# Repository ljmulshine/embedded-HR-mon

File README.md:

# embedded-HR-mon
Personal project that improves upon a previous breadboard based HR monitor project of mine.

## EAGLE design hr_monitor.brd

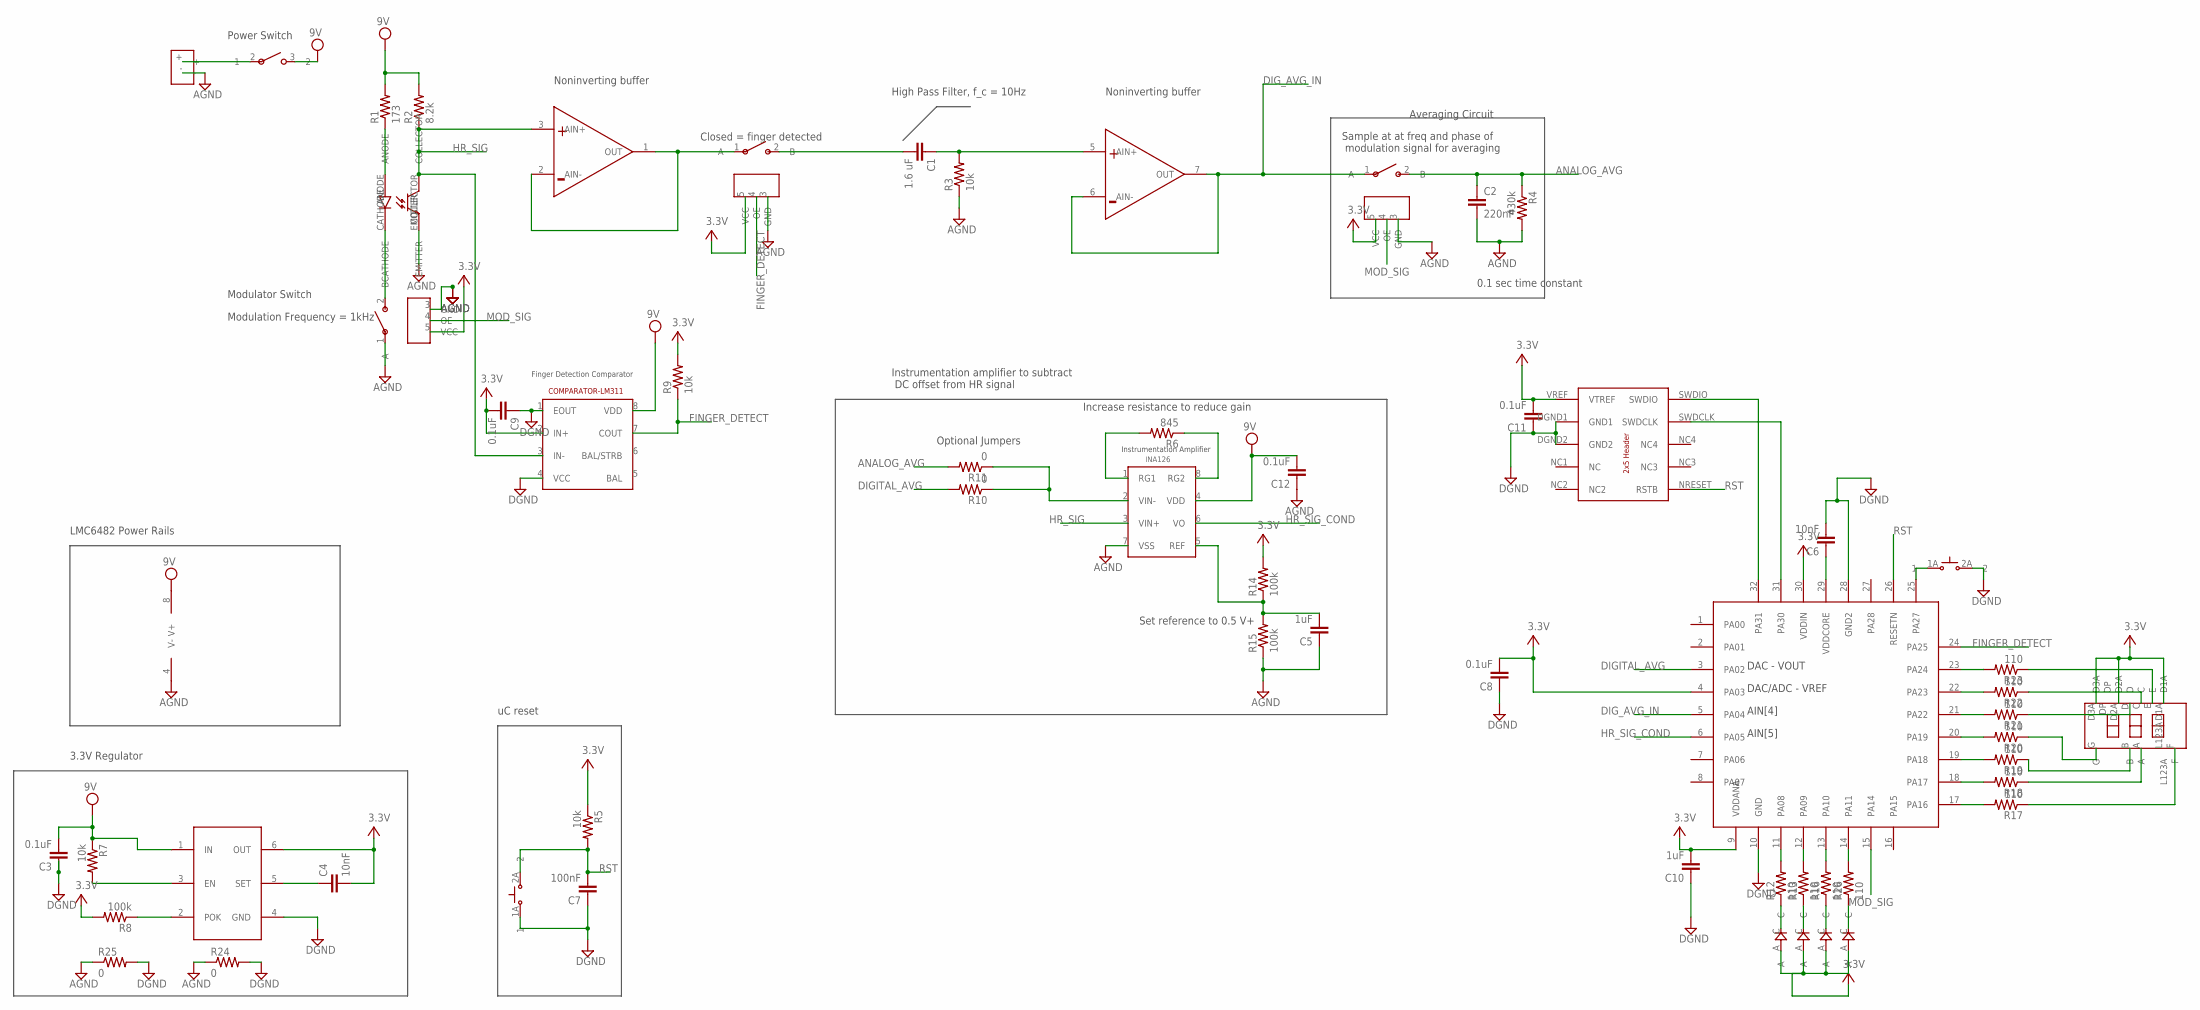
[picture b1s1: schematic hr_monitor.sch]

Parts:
C1: 1.6 uF; C0805
C2: 220nF; C0805
C3, C8, C9, C11, C12: 0.1uF; C0805
C4, C6: 10nF; C0805
C5, C10: 1uF; C0805
C7: 100nF; C0805
DBG1: DEBUGHEAD
R1: 173; R0805
R2: 8.2k; R0805
R3, R5, R7, R9: 10k; R0805
R4: 430k; R0805
R6: 845; R0805
R8, R14, R15: 100k; R0805
R10, R11, R24, R25: 0; R0805
R12, R13, R16, R17, R18, R19, R20, R21, R22, R23, R26: 110; R0805
U1: SAMD21E; TQFP32-08
U2: 3.3V_AS1363; SOT23-6
U$2, U$5, U$7: SPST; SOT23
U$3: INA126; SOIC-8
U$4: LM311; SOIC8
U$6: LMC6482; SOIC8
U$8, U$13: SWITCHPUSHBUTTON; KMR7-SWITCH
U$9, U$14, U$15, U$16: LED
U$10: 3DIG-7SEG-DISPLAY; 3-DIGIT-7SEG
U$11: PWR-CONN; THRU-HOLE-POWER
U$12: SWITCH2; DPDT-SLIDE-SWITCH
U$17: TCRT1000

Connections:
AGND: C2.2, C5.1, C12.1, R3.1, R4.2, R15.1, R24.1, R25.1, U$2.3 (GND), U$3.7 (VSS), U$5.1 (A), U$5.3 (GND), U$6.4 (V-), U$7.3 (GND), U$11.-, U$17.EMITTER
ANALOG_AVG: C2.1, R4.1, R11.2, U$7.2 (B)
DGND: C3.1, C6.2, C7.1, C8.1, C9.1, C10.1, C11.1, DBG1.DGND1 (GND1), DBG1.DGND2 (GND2), R24.2, R25.2, U1.10 (GND), U1.28 (GND2), U2.4 (GND), U$4.1 (EOUT), U$4.4 (VCC), U$8.1A (1), U$13.2A (2)
DIGITAL_AVG: R10.2, U1.3 (PA02)
DIG_AVG_IN: U1.5 (PA04), U$6.6 (AIN-), U$6.7 (OUT), U$7.1 (A)
FINGER_DETECT: R9.1, U1.24 (PA25), U$2.4 (OE), U$4.7 (COUT)
HR_SIG: R2.1, U$3.3 (VIN+), U$4.3 (IN-), U$6.3 (AIN+), U$17.COLLECTOR
HR_SIG_COND: U1.6 (PA05), U$3.6 (VO)
MOD_SIG: U1.15 (PA14), U$5.4 (OE), U$7.4 (OE)
unnamed: R1.1, U$17.ANODE
unnamed: U$5.2 (B), U$17.CATHODE
unnamed: C1.2, U$2.2 (B)
unnamed: R12.2, U1.11 (PA08)
unnamed: C1.1, R3.2, U$6.5 (AIN+)
unnamed: U$2.1 (A), U$6.1 (OUT), U$6.2 (AIN-)
unnamed: R7.2, U2.3 (EN)
unnamed: R8.1, U2.2 (POK)
unnamed: C4.1, U2.5 (SET)
unnamed: R6.2, U$3.1 (RG1)
unnamed: R6.1, U$3.8 (RG2)
unnamed: R10.1, R11.1, U$3.2 (VIN-)
unnamed: C5.2, R14.1, R15.2, U$3.5 (REF)
unnamed: C6.1, U1.29 (VDDCORE)
unnamed: R13.2, U1.12 (PA09)
unnamed: R16.2, U1.13 (PA10)
unnamed: R23.1, U$10.E
unnamed: R22.1, U$10.C
unnamed: R12.1, U$9.C
unnamed: R13.1, U$14.C
unnamed: R16.1, U$15.C
unnamed: R21.1, U$10.D
unnamed: R20.1, U$10.G
unnamed: R19.1, U$10.B
unnamed: R18.1, U$10.A
unnamed: R17.1, U$10.F
unnamed: R19.2, U1.19 (PA18)
unnamed: R17.2, U1.17 (PA16)
unnamed: R18.2, U1.18 (PA17)
unnamed: R20.2, U1.20 (PA19)
unnamed: R21.2, U1.21 (PA22)
unnamed: R22.2, U1.22 (PA23)
unnamed: R23.2, U1.23 (PA24)
unnamed: DBG1.SWDIO, U1.32 (PA31)
unnamed: DBG1.SWDCLK, U1.31 (PA30)
unnamed: U$11.+, U$12.2 (1)
unnamed: U1.25 (PA27), U$13.1A (1)
unnamed: R26.1, U$16.C
unnamed: R26.2, U1.14 (PA11)
RST: C7.2, DBG1.NRESET (RSTB), R5.2, U1.26 (RESETN), U$8.2A (2)
V+: C4.2, C8.2, C9.2, C10.2, C11.2, DBG1.VREF (VTREF), R5.1, R8.2, R9.2, R14.2, U1.4 (PA03), U1.9 (VDDANA), U1.30 (VDDIN), U2.6 (OUT), U$2.5 (VCC), U$4.2 (IN+), U$5.5 (VCC), U$7.5 (VCC), U$9.A, U$10.D1A, U$10.D2A, U$10.D3A, U$14.A, U$15.A, U$16.A
VDD: C3.2, C12.2, R1.2, R2.2, R7.1, U2.1 (IN), U$3.4 (VDD), U$4.8 (VDD), U$6.8 (V+), U$12.3 (2)

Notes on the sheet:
Finger Detection Comparator
LMC6482 Power Rails
Noninverting buffer
High Pass Filter, f_c = 10Hz
Modulator Switch
Modulation Frequency = 1kHz
Closed = finger detected
Averaging Circuit
Optional Jumpers
Sample at at freq and phase of modulation signal for averaging
0.1 sec time constant
Set reference to 0.5 V+
DAC - VOUT
DAC/ADC - VREF
AIN[4]
Increase resistance to reduce gain
Instrumentation amplifier to subtract DC offset from HR signal
3.3V Regulator
uC reset
AIN[5]
Power Switch

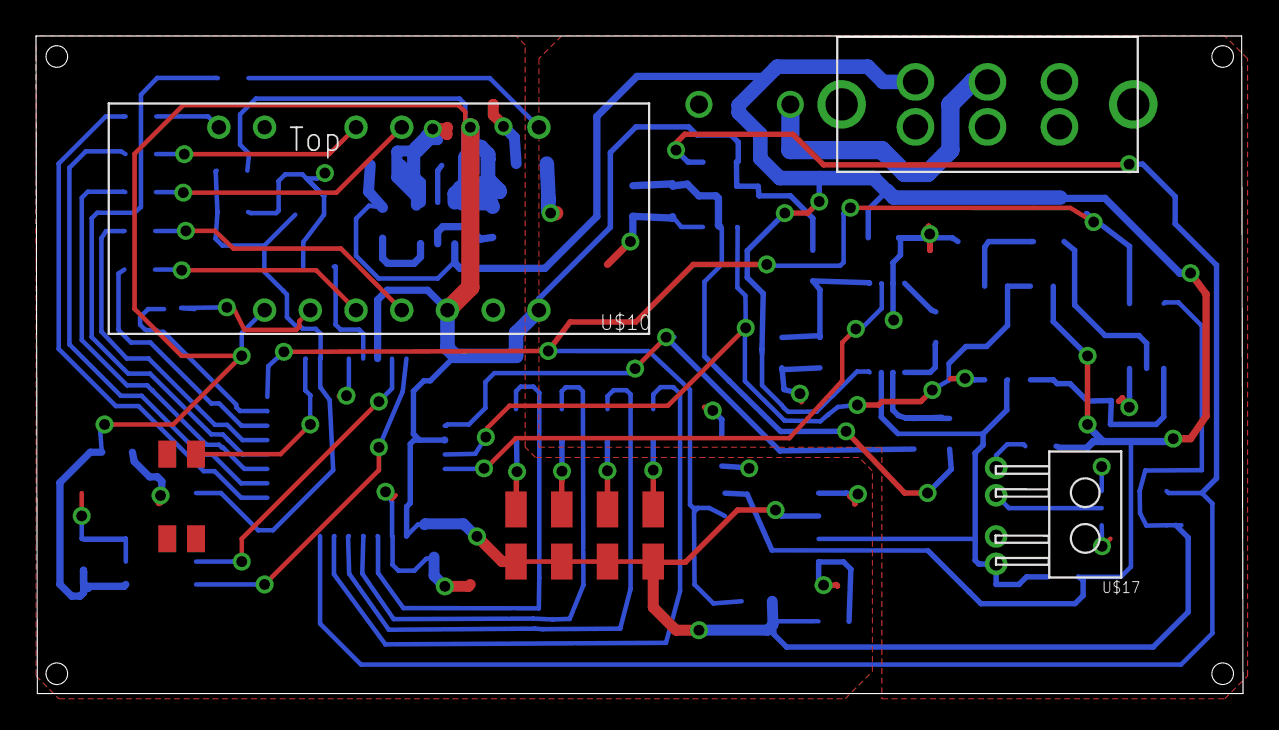
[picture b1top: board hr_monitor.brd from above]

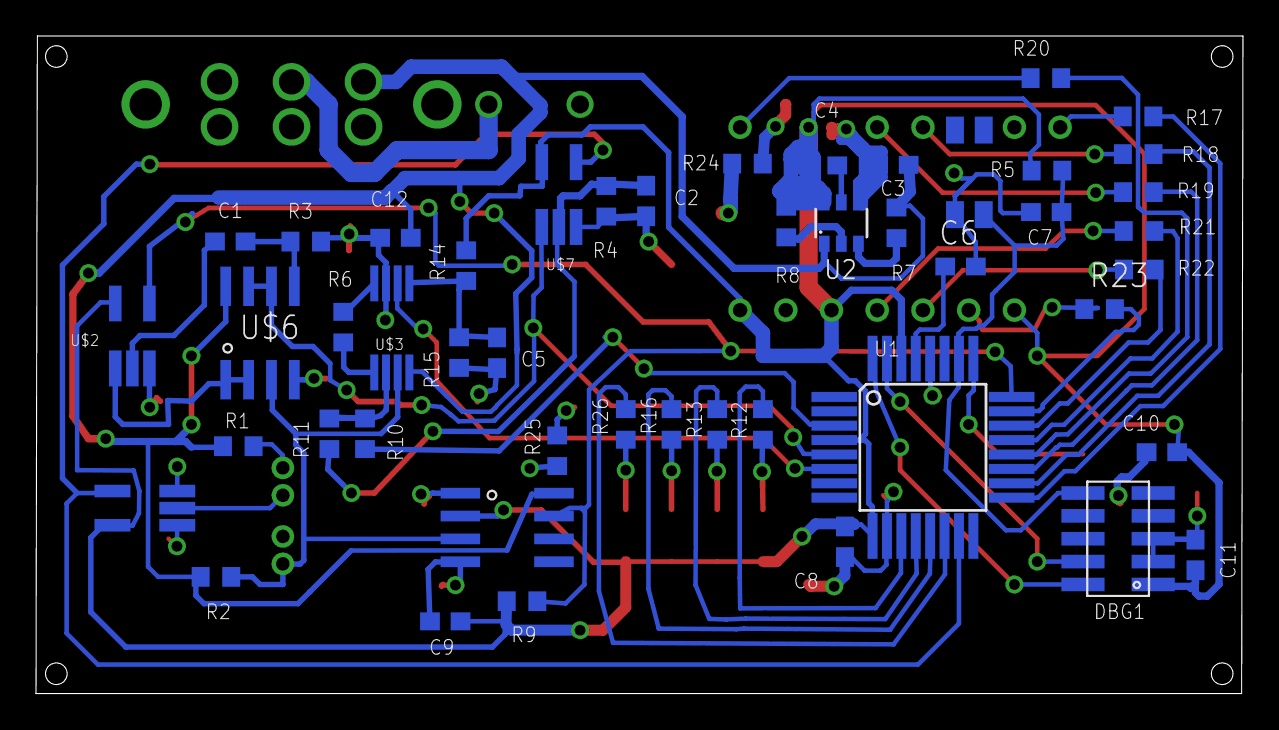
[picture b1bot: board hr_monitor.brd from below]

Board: 2 copper layers, 67.1 x 36.5 mm, 57 parts (48 on the bottom side), 51 nets.

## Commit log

2016-08-25 adding current project files
2016-08-30 adding tc functionality to firmware; experiencing some bugs, but could just be a result of using different hardware
2016-08-30 added firmware file
2016-08-31 enabled clock channel, need to test in the morning
